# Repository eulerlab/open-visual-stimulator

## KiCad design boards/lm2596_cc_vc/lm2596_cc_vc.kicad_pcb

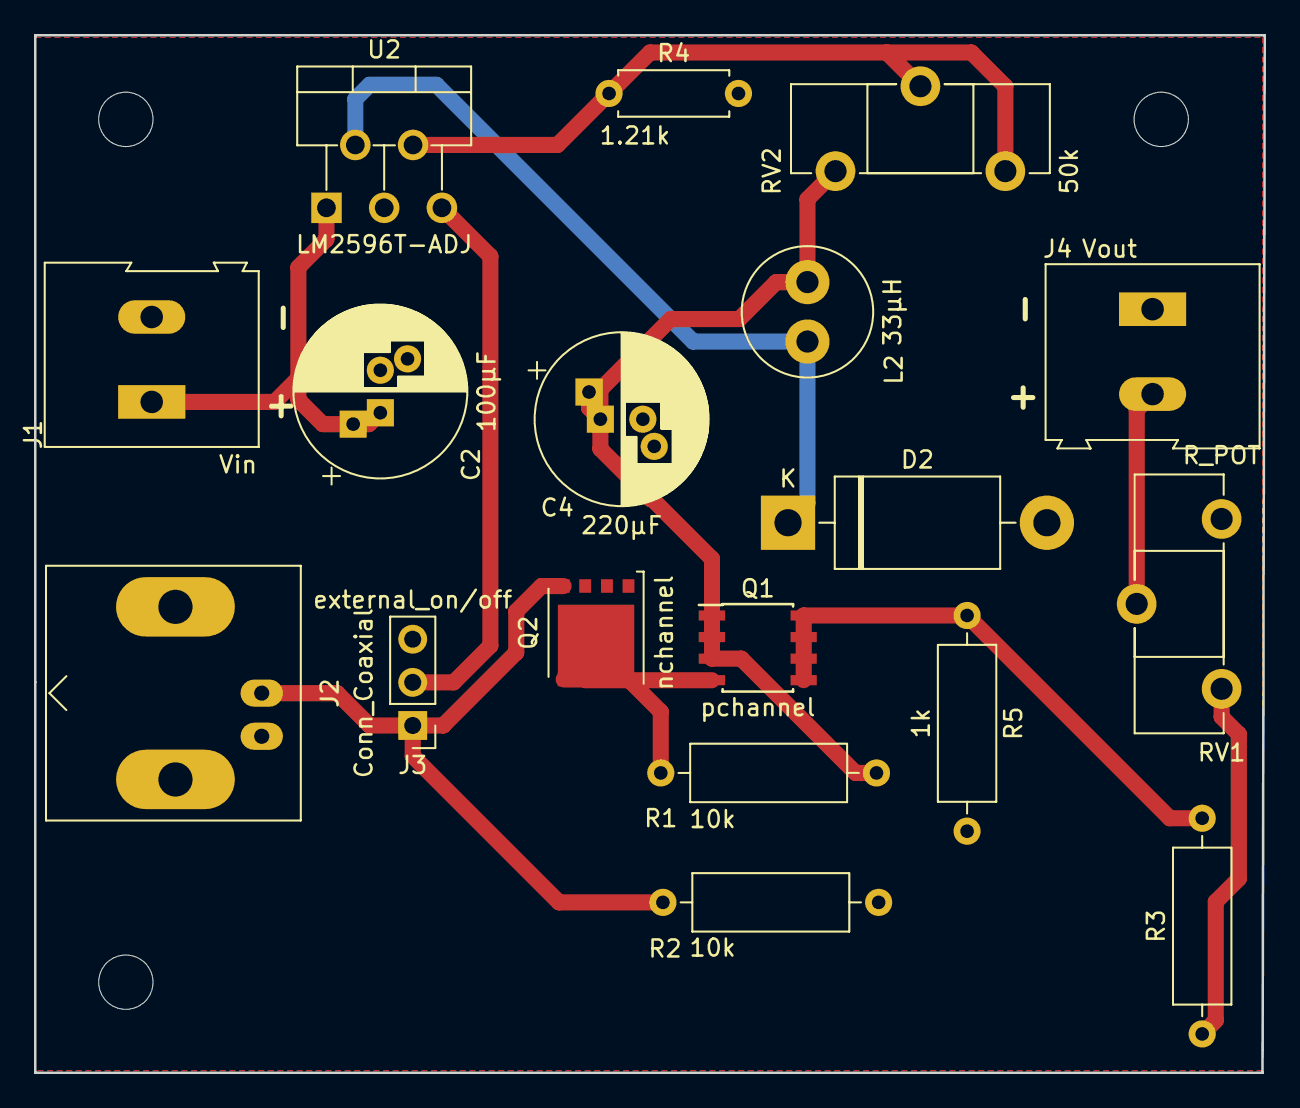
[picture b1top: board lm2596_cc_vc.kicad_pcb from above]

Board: 2 copper layers, 72.4 x 61.1 mm, 18 parts (0 on the bottom side), 11 nets.

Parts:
C2: 100µF; CP_Radial_D10.0mm_P2.50mm_P5.00mm
C4: 220µF; CP_Radial_D10.0mm_P2.50mm_P5.00mm
D2: 1N5822; D_DO-201AD_P15.24mm_Horizontal
J1: Vin; TerminalBlock_Altech_AK300-2_P5.00mm
J2: Conn_Coaxial; BNC_Amphenol_B6252HB-NPP3G-50_Horizontal
J3: external_on/off; PinHeader_1x03_P2.54mm_Vertical
J4: Vout; TerminalBlock_Altech_AK300-2_P5.00mm
L2: 33µH; L_Radial_D7.5mm_P3.50mm_Fastron_07P
Q1: pchannel; SOIC-8_3.9x4.9mm_P1.27mm
Q2: nchannel; TDSON-8-1
R1, R2: 10k; R_Axial_DIN0309_L9.0mm_D3.2mm_P12.70mm_Horizontal
R3: R; R_Axial_DIN0309_L9.0mm_D3.2mm_P12.70mm_Horizontal
R4: 1.21k; R_Axial_DIN0207_L6.3mm_D2.5mm_P7.62mm_Horizontal
R5: 1k; R_Axial_DIN0309_L9.0mm_D3.2mm_P12.70mm_Horizontal
RV1: R_POT; Potentiometer_Piher_PT-15-H25_Horizontal
RV2: 50k; Potentiometer_Piher_PT-15-H25_Horizontal
U2: LM2596T-ADJ; TO-220-5_P3.4x3.7mm_StaggerOdd_Lead3.8mm_Vertical

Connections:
+24V: C2.1, J1.1, U2.1
GND: C2.2, C4.2, D2.2, J1.2, J2.2, J3.3, J4.1, Q2.1, Q2.2, Q2.3, R2.1, R4.2, R5.2, U2.3
unnamed: C4.1, L2.2, Q1.1, Q1.2, Q1.3, R1.2, RV2.1
unnamed: D2.1, L2.1, U2.2
unnamed: J2.1, J3.1, Q2.4, R2.2
unnamed: J3.2, U2.5
unnamed: J4.2, RV1.2
unnamed: Q1.4, Q2.5, R1.1
unnamed: Q1.5, Q1.6, Q1.7, Q1.8, R3.2, R5.1
unnamed: R3.1, RV1.1
unnamed: R4.1, RV2.2, RV2.3, U2.4

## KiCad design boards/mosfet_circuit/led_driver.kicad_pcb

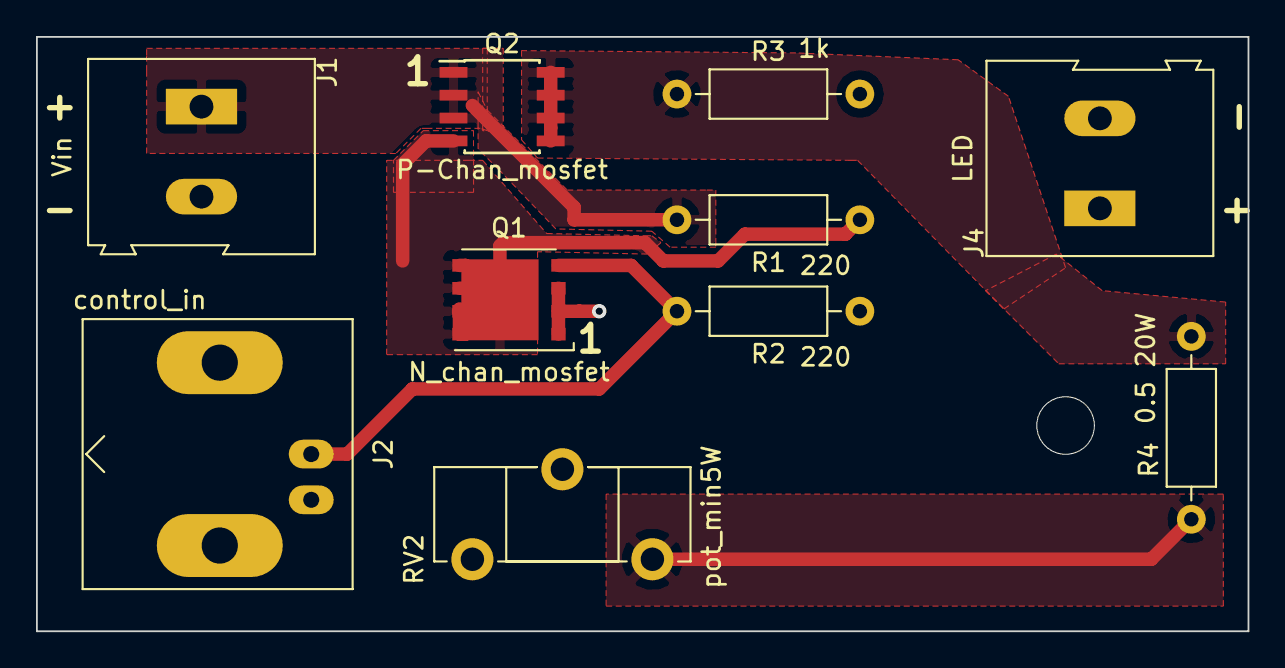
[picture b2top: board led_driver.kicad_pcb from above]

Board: 2 copper layers, 67.3 x 33.0 mm, 10 parts (0 on the bottom side), 7 nets.

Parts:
J1: Vin; TerminalBlock_Altech_AK300-2_P5.00mm
J2: control_in; BNC_Amphenol_B6252HB-NPP3G-50_Horizontal
J4: LED; TerminalBlock_Altech_AK300-2_P5.00mm
Q1: N_chan_mosfet; TDSON-8-1
Q2: P-Chan_mosfet; SOIC-8_3.9x4.9mm_P1.27mm
R1, R2: 220; R_Axial_DIN0207_L6.3mm_D2.5mm_P10.16mm_Horizontal
R3: 1k; R_Axial_DIN0207_L6.3mm_D2.5mm_P10.16mm_Horizontal
R4: 0.5 20W; R_Axial_DIN0207_L6.3mm_D2.5mm_P10.16mm_Horizontal
RV2: pot_min5W; Potentiometer_ACP_CA14-H5_Horizontal

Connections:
GND: J1.2, J2.2, J4.2, Q1.1, Q1.2, Q1.3, R2.1, R3.2
unnamed: J1.1, Q2.1, Q2.2, Q2.3, R1.2
unnamed: J2.1, Q1.4, R2.2
unnamed: J4.1, RV2.2
unnamed: Q1.5, Q2.4, R1.1
unnamed: Q2.5, Q2.6, Q2.7, Q2.8, R3.1, R4.2
unnamed: R4.1, RV2.3

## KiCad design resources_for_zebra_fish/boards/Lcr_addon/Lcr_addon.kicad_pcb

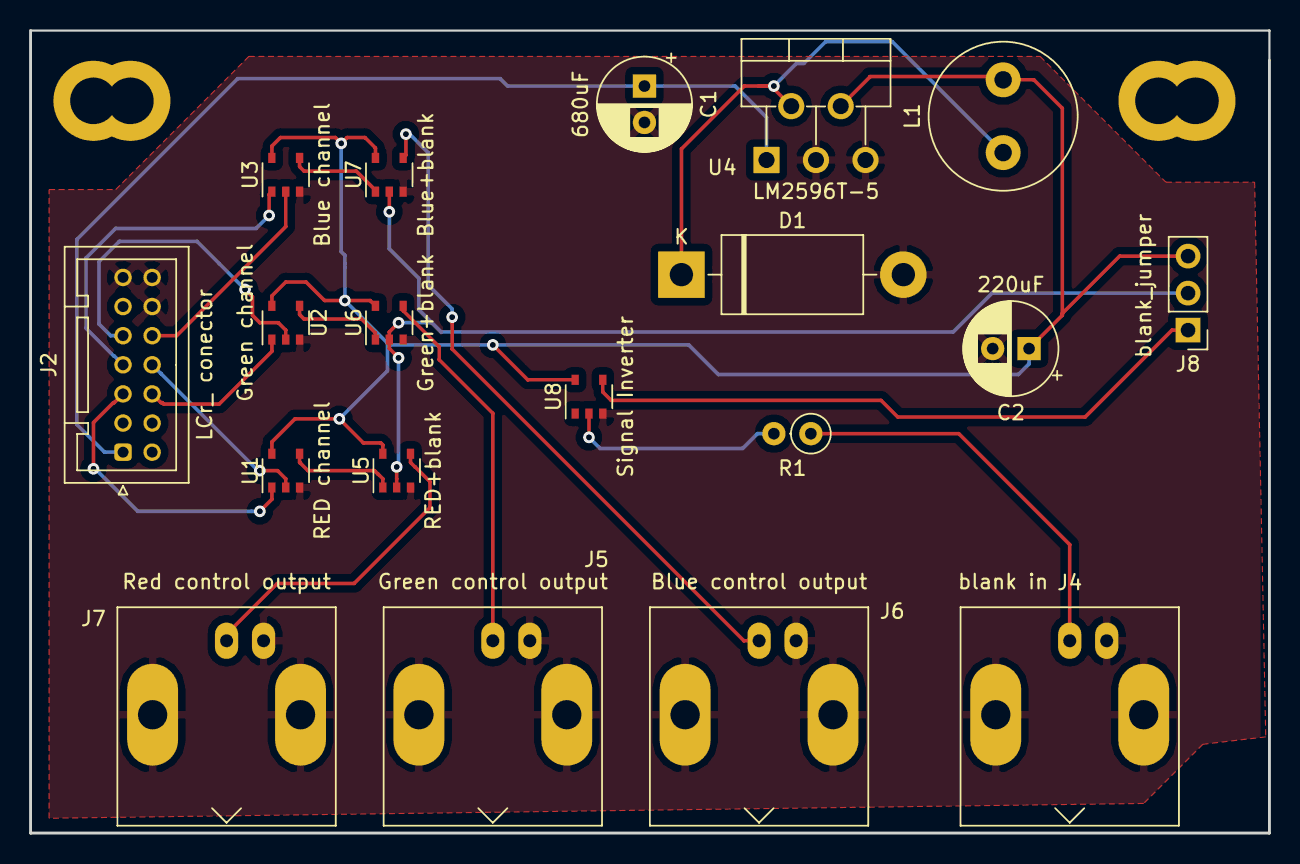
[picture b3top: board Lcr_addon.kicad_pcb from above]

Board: 2 copper layers, 85.1 x 55.1 mm, 19 parts (0 on the bottom side), 20 nets.

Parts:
C1: 680uF; CP_Radial_D6.3mm_P2.50mm
C2: 220uF; CP_Radial_D6.3mm_P2.50mm
D1: D_Schottky; D_DO-201AD_P15.24mm_Horizontal
J2: LCr_ conector; JST_PUD_B14B-PUDSS_2x07_P2.00mm_Vertical
J4: blank in; BNC_Amphenol_B6252HB-NPP3G-50_Horizontal
J5: Green control output; BNC_Amphenol_B6252HB-NPP3G-50_Horizontal
J6: Blue control output; BNC_Amphenol_B6252HB-NPP3G-50_Horizontal
J7: Red control output; BNC_Amphenol_B6252HB-NPP3G-50_Horizontal
J8: blank_jumper; PinHeader_1x03_P2.54mm_Vertical
L1: 33uH; L_Radial_D10.0mm_P5.00mm_Neosid_SD12_style3
R1: 1k; R_Axial_DIN0207_L6.3mm_D2.5mm_P2.54mm_Vertical
U1: RED channel; TSOP-5_1.65x3.05mm_P0.95mm
U2: Green channel; TSOP-5_1.65x3.05mm_P0.95mm
U3: Blue channel; TSOP-5_1.65x3.05mm_P0.95mm
U4: LM2596T-5; TO-220-5_P3.4x3.7mm_StaggerOdd_Lead3.8mm_Vertical
U5: RED+blank; TSOP-5_1.65x3.05mm_P0.95mm
U6: Green+blank; TSOP-5_1.65x3.05mm_P0.95mm
U7: Blue+blank; TSOP-5_1.65x3.05mm_P0.95mm
U8: Signal Inverter; TSOP-5_1.65x3.05mm_P0.95mm

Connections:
+12V: C1.1, J2.1, U4.1
GND: C1.2, C2.2, D1.2, J2.12, J2.13, J2.14, J4.2, J5.2, J6.2, J7.2, U1.3, U2.3, U3.3, U4.3, U4.5, U5.3, U6.3, U7.3, U8.3
unnamed: D1.1, L1.1, U4.2
unnamed: J2.5, U1.1
unnamed: J2.6, U2.1
unnamed: J2.7, U3.1
unnamed: J2.8, U1.2
unnamed: J2.9, U2.2
unnamed: J2.10, U3.2
unnamed: J4.1, R1.1
unnamed: J5.1, U6.4
unnamed: J6.1, U7.4
unnamed: J7.1, U5.4
unnamed: J8.1, U8.4
unnamed: J8.2, U5.2, U6.2, U7.2
unnamed: R1.2, U8.2
unnamed: U1.4, U5.1
unnamed: U2.4, U6.1
unnamed: U3.4, U7.1
VCC: C2.1, J8.3, L1.2, U1.5, U2.5, U3.5, U4.4, U5.5, U6.5, U7.5, U8.5

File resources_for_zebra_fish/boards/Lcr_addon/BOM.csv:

"Source:","/home/andre/Documents/repositories/amchagas/open-visual-stimulator/resources_for_zebra_fish/boards/Lcr_addon/Lcr_addon.sch"
"Date:","Thu 07 Mar 2019 18:06:58 GMT"
"Tool:","Eeschema 5.0.2-bee76a0~70~ubuntu18.04.1"
"Component Count:","19"
"Ref","Value","Footprint","Datasheet","Manufacturer","Vendor"
"C1","680uF","Capacitor_THT:CP_Radial_D6.3mm_P2.50mm","~","",""
"C2","220uF","Capacitor_THT:CP_Radial_D6.3mm_P2.50mm","~","",""
"D1","D_Schottky","Diode_THT:D_DO-201AD_P15.24mm_Horizontal","~","",""
"J2","LCr_ conector","Connector_JST:JST_PUD_B14B-PUDSS_2x07_P2.00mm_Vertical","~","",""
"J4","blank in","extra_Connector:BNC_Amphenol_B6252HB-NPP3G-50_Horizontal"," ~","",""
"J5","Green control output","extra_Connector:BNC_Amphenol_B6252HB-NPP3G-50_Horizontal"," ~","",""
"J6","Blue control output","extra_Connector:BNC_Amphenol_B6252HB-NPP3G-50_Horizontal"," ~","",""
"J7","Red control output","extra_Connector:BNC_Amphenol_B6252HB-NPP3G-50_Horizontal"," ~","",""
"J8","blank_jumper","Connector_PinHeader_2.54mm:PinHeader_1x03_P2.54mm_Vertical","~","",""
"L1","33uH","Inductor_THT:L_Radial_D10.0mm_P5.00mm_Neosid_SD12_style3","~","",""
"R1","1k","Resistor_THT:R_Axial_DIN0204_L3.6mm_D1.6mm_P7.62mm_Horizontal","~","",""
"U1","RED channel","Package_SO:TSOP-5_1.65x3.05mm_P0.95mm","http://www.ti.com/lit/sg/scyt129e/scyt129e.pdf","",""
"U2","Green channel","Package_SO:TSOP-5_1.65x3.05mm_P0.95mm","http://www.ti.com/lit/sg/scyt129e/scyt129e.pdf","",""
"U3","Blue channel","Package_SO:TSOP-5_1.65x3.05mm_P0.95mm","http://www.ti.com/lit/sg/scyt129e/scyt129e.pdf","",""
"U4","LM2596T-5","Package_TO_SOT_THT:TO-220-5_P3.4x3.7mm_StaggerOdd_Lead3.8mm_Vertical","http://www.ti.com/lit/ds/symlink/lm2596.pdf","",""
"U5","RED+blank","Package_SO:TSOP-5_1.65x3.05mm_P0.95mm","http://www.ti.com/lit/sg/scyt129e/scyt129e.pdf","",""
"U6","Green+blank","Package_SO:TSOP-5_1.65x3.05mm_P0.95mm","http://www.ti.com/lit/sg/scyt129e/scyt129e.pdf","",""
"U7","Blue+blank","Package_SO:TSOP-5_1.65x3.05mm_P0.95mm","http://www.ti.com/lit/sg/scyt129e/scyt129e.pdf","",""
"U8","74AHC1G04","Package_SO:TSOP-5_1.65x3.05mm_P0.95mm","http://www.ti.com/lit/sg/scyt129e/scyt129e.pdf","",""
